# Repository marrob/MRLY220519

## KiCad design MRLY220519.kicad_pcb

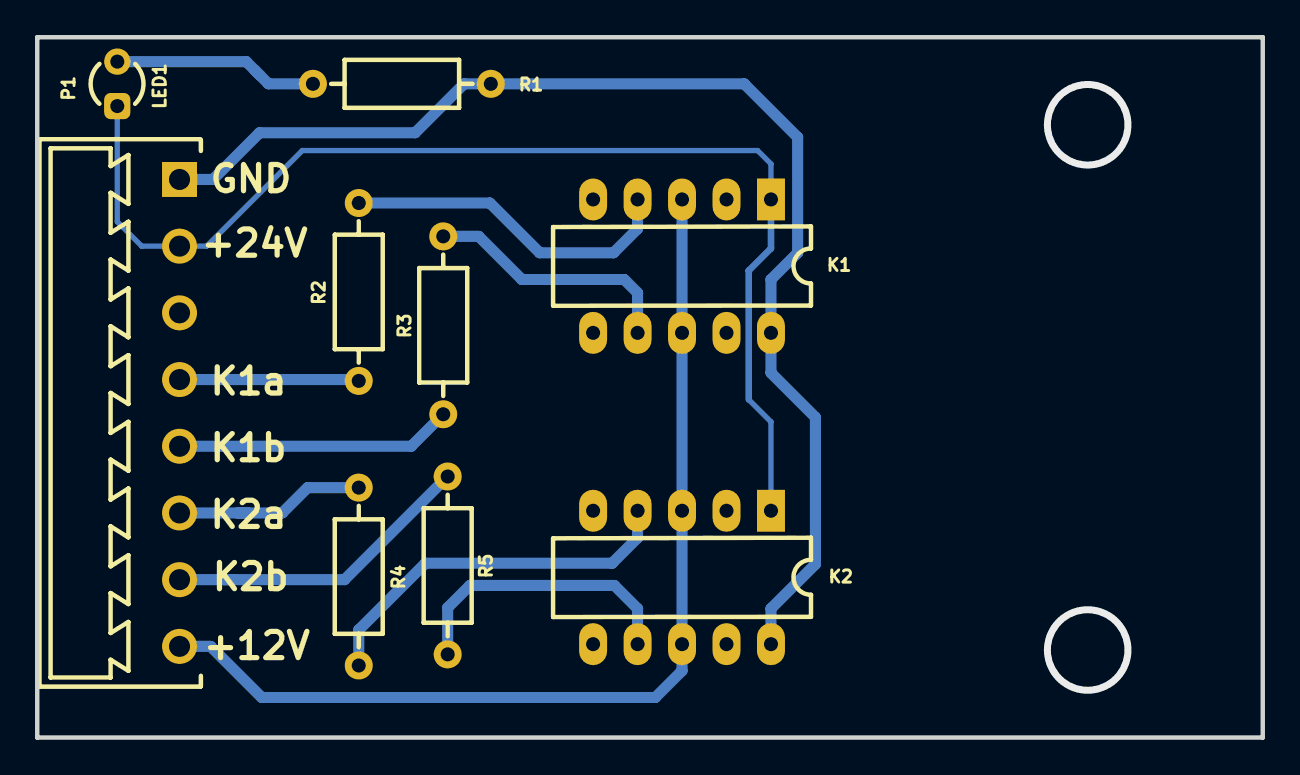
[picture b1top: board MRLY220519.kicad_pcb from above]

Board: 2 copper layers, 70.0 x 40.0 mm, 9 parts (0 on the bottom side), 12 nets.

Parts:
K1, K2: OMRON G6H-2-100
LED1: 3mm Green; LED RAD GRE 3mm
P1: Terminal Block 8 3.81 Straight; Terminal Block 01x08 P3.81 Horizontal
R1: Resistor 0207 10K0; R0207 Axial Horizontal
R2, R3, R4, R5: Resistor 0207 1K00; R0207 Axial Horizontal

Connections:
/+12V: K1.3, K1.8, K2.3, K2.8, P1.8
/+24V: K1.1, K2.1, LED1.2 (A), P1.2
/K1a: P1.4, R2.2
/K1b: P1.5, R3.2
/K2a: P1.6, R4.2
/K2b: P1.7, R5.2
GND: K1.10, K2.10, P1.1 (Pin_a1), R1.2
unnamed: K1.4, R2.1
unnamed: K1.7, R3.1
unnamed: K2.4, R4.1
unnamed: K2.7, R5.1
unnamed: LED1.1 (K), R1.1

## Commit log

2022-05-20 first
2022-05-20 updat
